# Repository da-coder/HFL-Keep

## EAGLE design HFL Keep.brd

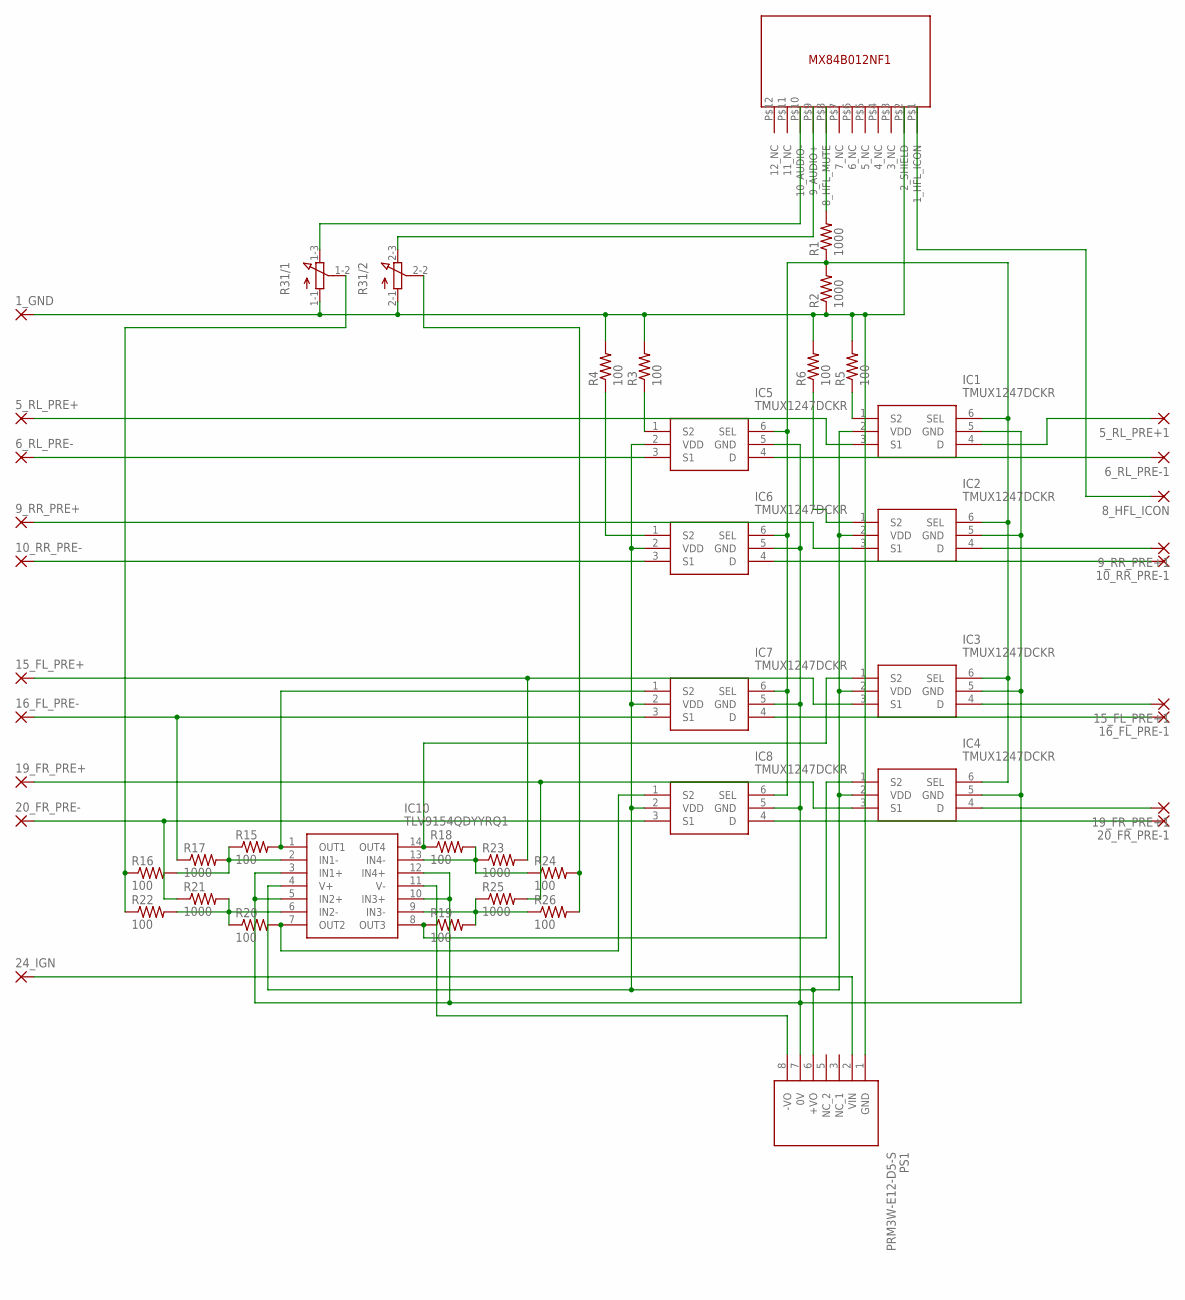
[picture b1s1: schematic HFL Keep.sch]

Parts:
1_GND, 5_RL_PRE+, 5_RL_PRE+1, 6_RL_PRE-, 6_RL_PRE-1, 8_HFL_ICON, 9_RR_PRE+, 9_RR_PRE+1, 10_RR_PRE-, 10_RR_PRE-1, 15_FL_PRE+, 15_FL_PRE+1, 16_FL_PRE-, 16_FL_PRE-1, 19_FR_PRE+, 19_FR_PRE+1, 20_FR_PRE-, 20_FR_PRE-1, 24_IGN: 3,81/1,4
IC1, IC2, IC3, IC4, IC5, IC6, IC7, IC8: TMUX1247DCKR; SOT65P210X110-6N
IC10: TLV9154QDYYRQ1; SOP50P326X110-14N
PS1: PRM3W-E12-D5-S; PRM3WE12D5S
R1, R2, R17, R21, R23, R25: 1000; 0204/7
R3, R4, R5, R6, R15, R16, R18, R19, R20, R22, R24, R26: 100; 0204/7
R31: 3RP/1610G
U$1: MX84B012NF1

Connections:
unnamed: 6_RL_PRE-1.1, IC5.4 (D)
unnamed: IC5.1 (S2), R3.1
unnamed: 1_GND.1, PS1.1 (GND), R2.1, R3.2, R4.2, R5.2, R6.2, R31.1-1 (A), R31.2-1 (A), U$1.P$2 (2_SHIELD)
unnamed: IC6.1 (S2), R4.1
unnamed: IC2.1 (S2), R6.1
unnamed: 8_HFL_ICON.1, U$1.P$1 (1_HFL_ICON)
unnamed: IC1.1 (S2), R5.1
unnamed: 15_FL_PRE+.1, IC3.3 (S1), R23.2
unnamed: 5_RL_PRE+1.1, IC1.4 (D)
unnamed: IC1.6 (SEL), IC2.6 (SEL), IC3.6 (SEL), IC4.6 (SEL), IC5.6 (SEL), IC6.6 (SEL), IC7.6 (SEL), IC8.6 (SEL), R1.1, R2.2
unnamed: 9_RR_PRE+1.1, IC2.4 (D)
unnamed: R16.1, R22.1, R31.1-2 (S)
unnamed: IC1.2 (VDD), IC2.2 (VDD), IC3.2 (VDD), IC4.2 (VDD), IC5.2 (VDD), IC6.2 (VDD), IC7.2 (VDD), IC8.2 (VDD), IC10.4 (V+), PS1.6 (+VO)
unnamed: 24_IGN.1, PS1.2 (VIN)
unnamed: 19_FR_PRE+.1, IC4.3 (S1), R25.2
unnamed: 20_FR_PRE-1.1, IC8.4 (D)
unnamed: 10_RR_PRE-.1, IC6.3 (S1)
unnamed: 20_FR_PRE-.1, IC8.3 (S1), R21.1
unnamed: IC10.11 (V-), PS1.8 (-VO)
unnamed: 5_RL_PRE+.1, IC1.3 (S1)
unnamed: R31.2-3 (E), U$1.P$9 (9_AUDIO+)
unnamed: R24.2, R26.2, R31.2-2 (S)
unnamed: 9_RR_PRE+.1, IC2.3 (S1)
unnamed: 15_FL_PRE+1.1, IC3.4 (D)
unnamed: 19_FR_PRE+1.1, IC4.4 (D)
unnamed: 16_FL_PRE-.1, IC7.3 (S1), R17.1
unnamed: 10_RR_PRE-1.1, IC6.4 (D)
unnamed: IC1.5 (GND), IC2.5 (GND), IC3.5 (GND), IC4.5 (GND), IC5.5 (GND), IC6.5 (GND), IC7.5 (GND), IC8.5 (GND), IC10.3 (IN1+), IC10.5 (IN2+), IC10.10 (IN3+), IC10.12 (IN4+), PS1.7 (0V)
unnamed: 16_FL_PRE-1.1, IC7.4 (D)
unnamed: 6_RL_PRE-.1, IC5.3 (S1)
unnamed: R31.1-3 (E), U$1.P$10 (10_AUDIO-)
unnamed: R1.2, U$1.P$8 (8_HFL_MUTE)
unnamed: IC10.2 (IN1-), R15.1, R16.2, R17.2
unnamed: IC7.1 (S2), IC10.1 (OUT1), R15.2
unnamed: IC3.1 (S2), IC10.14 (OUT4), R18.1
unnamed: IC4.1 (S2), IC10.8 (OUT3), R19.1
unnamed: IC8.1 (S2), IC10.7 (OUT2), R20.2
unnamed: IC10.9 (IN3-), R19.2, R25.1, R26.1
unnamed: IC10.6 (IN2-), R20.1, R21.2, R22.2
unnamed: IC10.13 (IN4-), R18.2, R23.1, R24.1

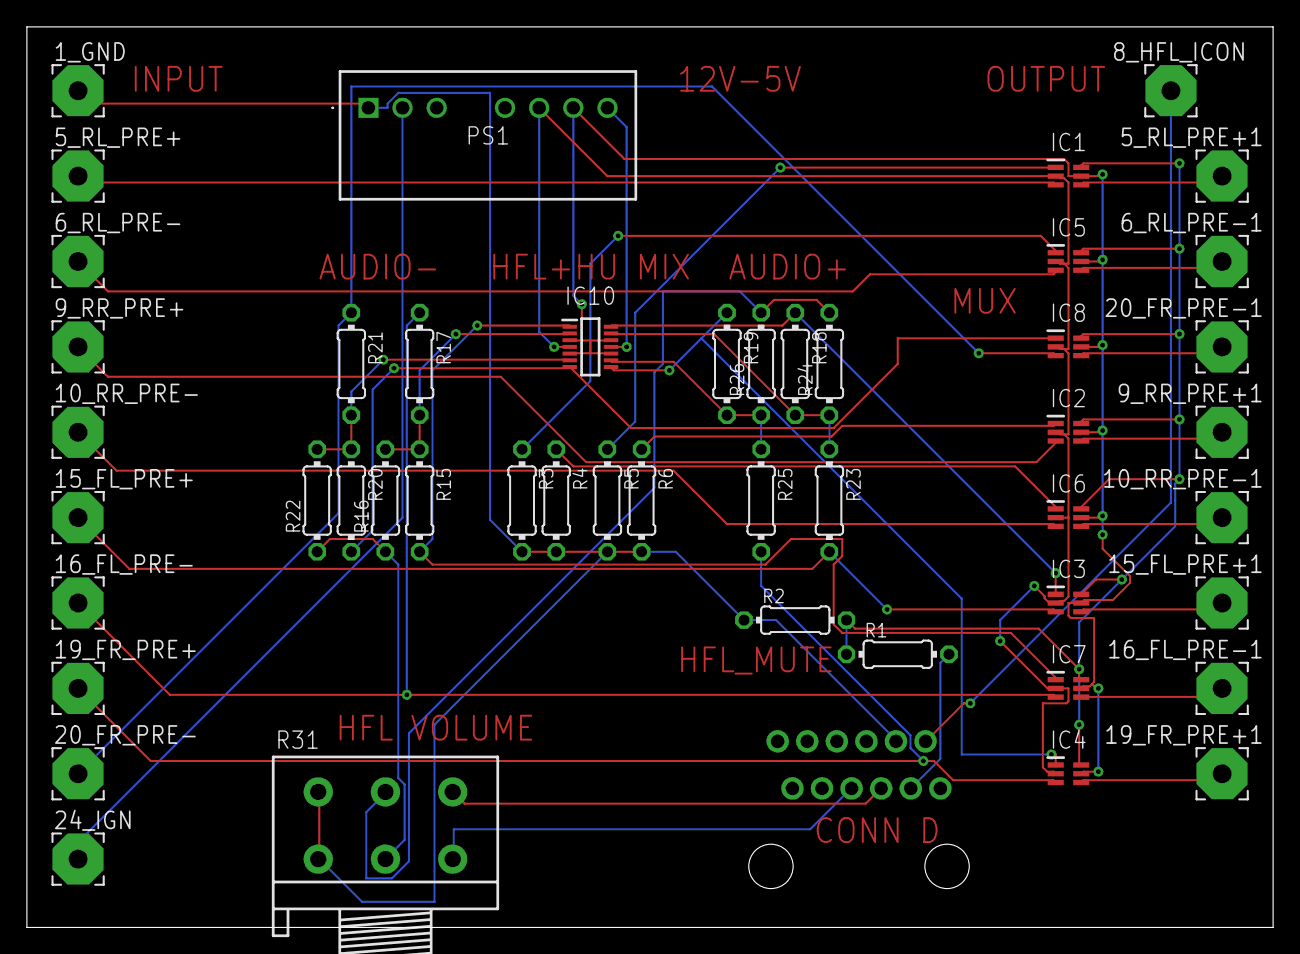
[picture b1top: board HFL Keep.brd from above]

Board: 2 copper layers, 92.7 x 67.0 mm, 49 parts (0 on the bottom side), 40 nets.

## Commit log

2024-01-31 forgot a few files
